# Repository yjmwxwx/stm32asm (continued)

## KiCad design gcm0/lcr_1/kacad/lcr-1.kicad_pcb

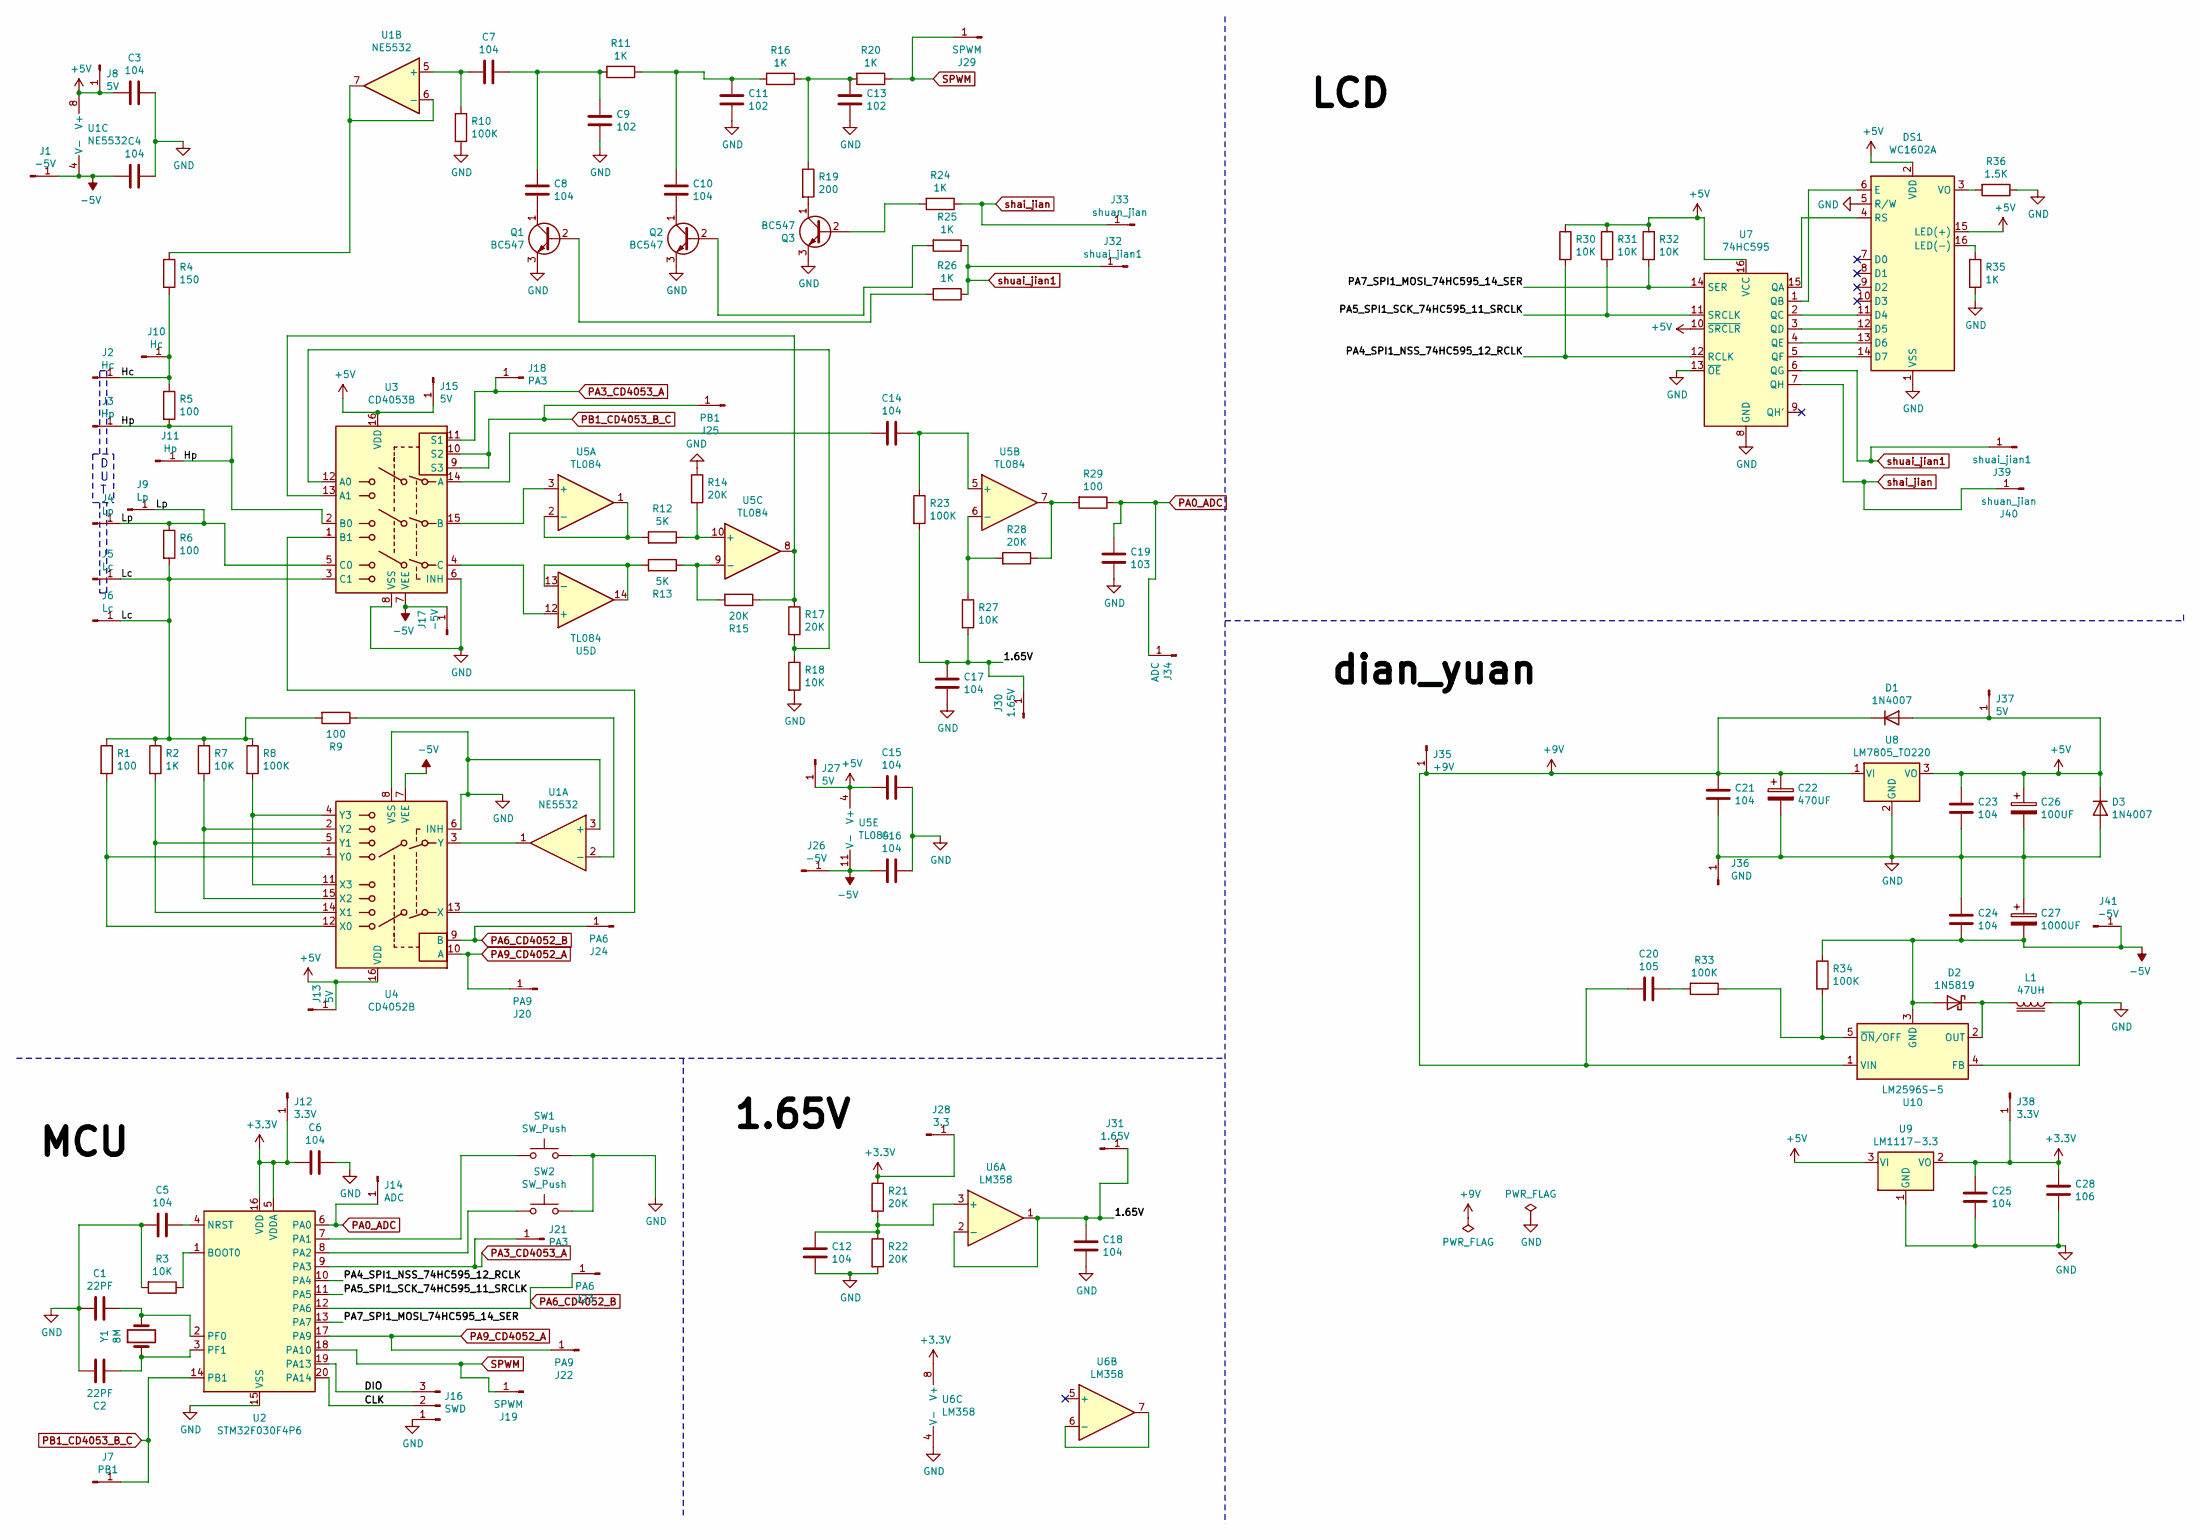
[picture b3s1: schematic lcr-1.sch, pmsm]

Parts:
C1, C2: 22PF; C_0805_2012Metric_Pad1.18x1.45mm_HandSolder
C3, C4, C5, C6, C7, C8, C10, C12, C14, C15, C16, C17, C18, C21, C23, C24, C25: 104; C_Disc_D3.0mm_W2.0mm_P2.50mm
C9, C11, C13: 102; C_Disc_D3.0mm_W2.0mm_P2.50mm
C19: 103; C_Disc_D3.0mm_W2.0mm_P2.50mm
C20: 105; C_0805_2012Metric_Pad1.18x1.45mm_HandSolder
C22: 470UF; CP_Radial_D10.0mm_P3.50mm
C26: 100UF; CP_Radial_D10.0mm_P3.50mm
C27: 1000UF; CP_Radial_D10.0mm_P3.50mm
C28: 106; C_0805_2012Metric_Pad1.18x1.45mm_HandSolder
D1, D3: 1N4007; D_DO-41_SOD81_P10.16mm_Horizontal
D2: 1N5819; D_SMA_Handsoldering
DS1: WC1602A
J1, J17, J26, J41: -5V; Pin_D0.7mm_L6.5mm_W1.8mm_FlatFork
J2, J10: Hc; Pin_D1.3mm_L11.0mm_LooseFit
J3, J11: Hp; Pin_D1.3mm_L11.0mm_LooseFit
J4, J9: Lp; Pin_D1.3mm_L11.0mm_LooseFit
J5, J6: Lc; Pin_D1.3mm_L11.0mm_LooseFit
J7, J25: PB1; Pin_D0.7mm_L6.5mm_W1.8mm_FlatFork
J8, J13, J15, J27, J37: 5V; Pin_D0.7mm_L6.5mm_W1.8mm_FlatFork
J12, J38: 3.3V; Pin_D0.7mm_L6.5mm_W1.8mm_FlatFork
J14, J34: ADC; Pin_D0.7mm_L6.5mm_W1.8mm_FlatFork
J16: SWD; PinHeader_1x03_P2.54mm_Vertical
J18, J21: PA3; Pin_D0.7mm_L6.5mm_W1.8mm_FlatFork
J19, J29: SPWM; Pin_D0.7mm_L6.5mm_W1.8mm_FlatFork
J20, J22: PA9; Pin_D0.7mm_L6.5mm_W1.8mm_FlatFork
J23, J24: PA6; Pin_D0.7mm_L6.5mm_W1.8mm_FlatFork
J28: 3.3; Pin_D0.7mm_L6.5mm_W1.8mm_FlatFork
J30, J31: 1.65V; Pin_D0.7mm_L6.5mm_W1.8mm_FlatFork
J32, J39: shuai_jian1; Pin_D0.7mm_L6.5mm_W1.8mm_FlatFork
J33, J40: shuan_jian; Pin_D0.7mm_L6.5mm_W1.8mm_FlatFork
J35: +9V; Pin_D1.3mm_L11.0mm_LooseFit
J36: GND; Pin_D1.3mm_L11.0mm_LooseFit
L1: 47UH; L_Radial_D10.0mm_P5.00mm_Fastron_07P
Q1, Q2, Q3: BC547; TO-92_Inline_Wide
R1, R5, R6, R9, R29: 100; R_Axial_DIN0204_L3.6mm_D1.6mm_P2.54mm_Vertical
R2, R11, R16, R20, R24, R25, R26, R35: 1K; R_Axial_DIN0204_L3.6mm_D1.6mm_P2.54mm_Vertical
R3, R7, R18, R27, R30, R31, R32: 10K; R_Axial_DIN0204_L3.6mm_D1.6mm_P2.54mm_Vertical
R4: 150; R_Axial_DIN0204_L3.6mm_D1.6mm_P2.54mm_Vertical
R8, R10, R23, R33, R34: 100K; R_Axial_DIN0204_L3.6mm_D1.6mm_P2.54mm_Vertical
R12, R13: 5K; R_Axial_DIN0204_L3.6mm_D1.6mm_P2.54mm_Vertical
R14, R15, R17, R21, R22, R28: 20K; R_Axial_DIN0204_L3.6mm_D1.6mm_P2.54mm_Vertical
R19: 200; R_Axial_DIN0204_L3.6mm_D1.6mm_P2.54mm_Vertical
R36: 1.5K; R_Axial_DIN0204_L3.6mm_D1.6mm_P2.54mm_Vertical
SW1, SW2: SW_Push; SW_PUSH_6mm_H7.3mm
U1: NE5532; DIP-8_W7.62mm
U2: STM32F030F4P6; TSSOP-20_4.4x6.5mm_P0.65mm
U3: CD4053B; DIP-16_W7.62mm
U4: CD4052B; DIP-16_W7.62mm
U5: TL084; DIP-14_W7.62mm
U6: LM358; DIP-8_W7.62mm
U7: 74HC595; DIP-16_W7.62mm
U8: LM7805_TO220; TO-220-3_Vertical
U9: LM1117-3.3; SOT-223-3_TabPin2
U10: LM2596S-5; TO-263-5_TabPin3
Y1: 8M; Crystal_HC49-4H_Vertical

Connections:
+3V3: C6.2, C25.1, C28.1, J12.1, J28.1, J38.1, R21.1, U2.5 (VDDA), U2.16 (VDD), U6.8 (V+), U9.2 (VO)
+5V: C3.2, C15.2, C23.1, C26.1, D1.2 (A), D3.1 (K), DS1.2 (VDD), DS1.15 (LED(+)), J8.1, J13.1, J15.1, J27.1, J37.1, R30.1, R31.1, R32.1, U1.8 (V+), U3.16 (VDD), U4.16 (VDD), U5.4 (V+), U7.10 (~SRCLR), U7.16 (VCC), U8.3 (VO), U9.3 (VI)
+9V: C20.2, C21.1, C22.1, D1.1 (K), J35.1, U8.1 (VI), U10.1 (VIN)
-5V: C4.2, C16.2, C24.2, C27.2, D2.2 (A), J1.1, J17.1, J26.1, J41.1, R34.1, U1.4 (V-), U3.7 (VEE), U4.7 (VEE), U5.11 (V-), U10.3 (GND)
/1.65V: C17.1, C18.1, J30.1, J31.1, R23.2, R27.2, U6.1, U6.2 (-)
/CLK: J16.2, U2.20 (PA14)
/DIO: J16.3, U2.19 (PA13)
/Hc: J2.1, J10.1, R4.2, R5.1
/Hp: J3.1, J11.1, R5.2, U3.2 (B0)
/Lc: J5.1, J6.1, R1.1, R2.1, R6.2, R7.1, R8.1, R9.2, U3.3 (C1)
/Lp: J4.1, J9.1, R6.1, U3.5 (C0)
/PA4_SPI1_NSS_74HC595_12_RCLK: R30.2, U2.10 (PA4), U7.12 (RCLK)
/PA5_SPI1_SCK_74HC595_11_SRCLK: R31.2, U2.11 (PA5), U7.11 (SRCLK)
/PA7_SPI1_MOSI_74HC595_14_SER: R32.2, U2.13 (PA7), U7.14 (SER)
GND: C1.2, C2.1, C3.1, C4.1, C5.2, C6.1, C9.2, C11.2, C12.2, C13.2, C15.1, C16.1, C17.2, C18.2, C19.2, C21.2, C22.2, C23.2, C24.1, C25.2, C26.2, C27.1, C28.2, D3.2 (A), DS1.1 (VSS), DS1.5 (R/W), J16.1, J36.1, L1.1, Q1.3 (E), Q2.3 (E), Q3.3 (E), R3.2, R10.2, R14.1, R18.2, R22.2, R35.2, R36.1, SW1.2, SW2.2, U1.3 (+), U2.15 (VSS), U3.6 (INH), U3.8 (VSS), U4.6 (INH), U4.8 (VSS), U6.4 (V-), U7.8 (GND), U7.13 (~OE), U8.2 (GND), U9.1 (GND), U10.4 (FB)
unnamed: C1.1, U2.2 (PF0), Y1.2
unnamed: C2.2, U2.3 (PF1), Y1.1
unnamed: C5.1, U2.4 (NRST)
unnamed: C7.1, C8.1, C9.1, R11.2
unnamed: C7.2, R10.1, U1.5 (+)
unnamed: C8.2, Q1.1 (C)
unnamed: C10.1, C11.1, R11.1, R16.2
unnamed: C10.2, Q2.1 (C)
unnamed: C12.1, R21.2, R22.1, U6.3 (+)
unnamed: C13.1, R16.1, R19.1, R20.2
unnamed: C14.1, R23.1, U5.5 (+)
unnamed: C14.2, U3.14 (A)
unnamed: C20.1, R33.2
unnamed: D2.1 (K), L1.2, U10.2 (OUT)
unnamed: DS1.3 (VO), R36.2
unnamed: DS1.4 (RS), U7.15 (QA)
unnamed: DS1.6 (E), U7.1 (QB)
unnamed: DS1.11 (D4), U7.2 (QC)
unnamed: DS1.12 (D5), U7.3 (QD)
unnamed: DS1.13 (D6), U7.4 (QE)
unnamed: DS1.14 (D7), U7.5 (QF)
unnamed: DS1.16 (LED(-)), R35.1
unnamed: Q1.2 (B), R26.2
unnamed: Q2.2 (B), R25.2
unnamed: Q3.1 (C), R19.2
unnamed: Q3.2 (B), R24.2
unnamed: R1.2, U4.1 (Y0), U4.12 (X0)
unnamed: R2.2, U4.5 (Y1), U4.14 (X1)
unnamed: R3.1, U2.1 (BOOT0)
unnamed: R4.1, U1.6 (-), U1.7
unnamed: R7.2, U4.2 (Y2), U4.15 (X2)
unnamed: R8.2, U4.4 (Y3), U4.11 (X3)
unnamed: R9.1, U1.2 (-)
unnamed: R12.1, R14.2, U5.10 (+)
unnamed: R12.2, U5.1, U5.2 (-)
unnamed: R13.1, R15.2, U5.9 (-)
unnamed: R13.2, U5.13 (-), U5.14
unnamed: R15.1, R17.1, U3.13 (A1), U5.8
unnamed: R17.2, R18.1, U3.12 (A0)
unnamed: R27.1, R28.2, U5.6 (-)
unnamed: R28.1, R29.2, U5.7
unnamed: R33.1, R34.2, U10.5 (~ON~/OFF)
unnamed: SW1.1, U2.7 (PA1)
unnamed: SW2.1, U2.8 (PA2)
unnamed: U1.1, U4.3 (Y)
unnamed: U3.1 (B1), U4.13 (X)
unnamed: U3.4 (C), U5.12 (+)
unnamed: U3.15 (B), U5.3 (+)
unnamed: U6.6 (-), U6.7
PA0_ADC: C19.1, J14.1, J34.1, R29.1, U2.6 (PA0)
PA3_CD4053_A: J18.1, J21.1, U2.9 (PA3), U3.11 (S1)
PA6_CD4052_B: J23.1, J24.1, U2.12 (PA6), U4.9 (B)
PA9_CD4052_A: J20.1, J22.1, U2.17 (PA9), U4.10 (A)
PB1_CD4053_B_C: J7.1, J25.1, U2.14 (PB1), U3.9 (S3), U3.10 (S2)
SPWM: J19.1, J29.1, R20.1, U2.18 (PA10)
shai_jian: J33.1, J40.1, R24.1, U7.7 (QH)
shuai_jian1: J32.1, J39.1, R25.1, R26.1, U7.6 (QG)

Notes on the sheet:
D U T

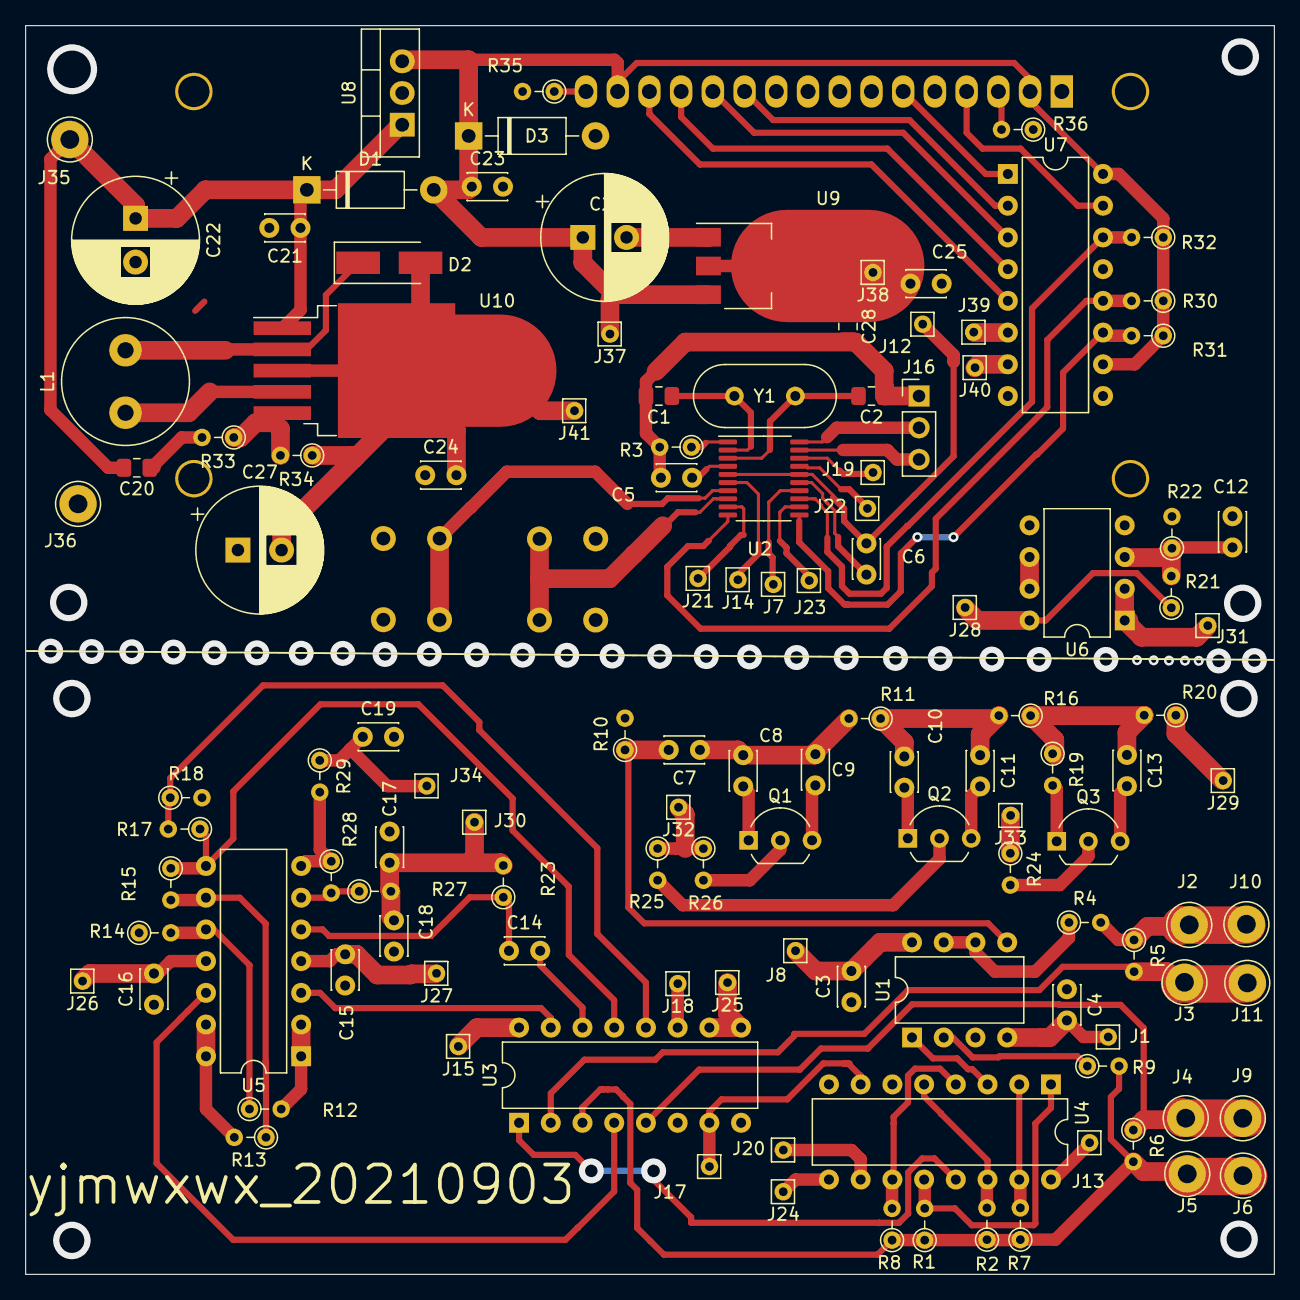
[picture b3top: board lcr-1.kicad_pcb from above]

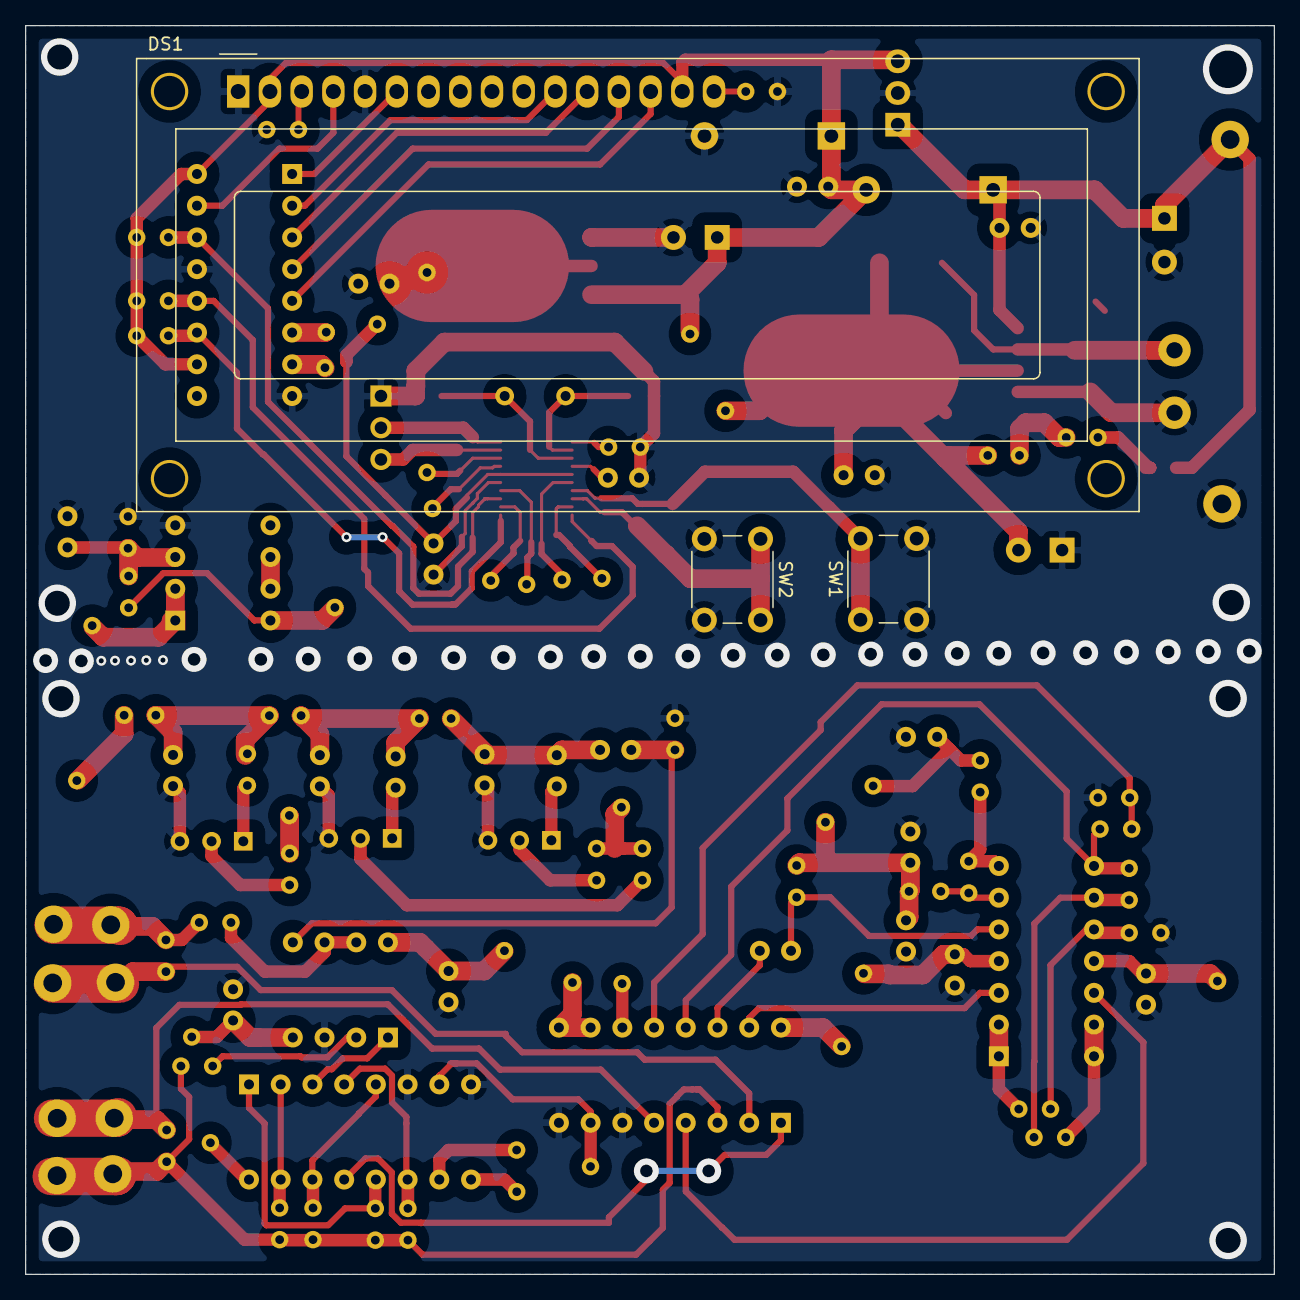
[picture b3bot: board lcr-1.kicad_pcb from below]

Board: 2 copper layers, 100.0 x 100.0 mm, 126 parts (3 on the bottom side), 72 nets.

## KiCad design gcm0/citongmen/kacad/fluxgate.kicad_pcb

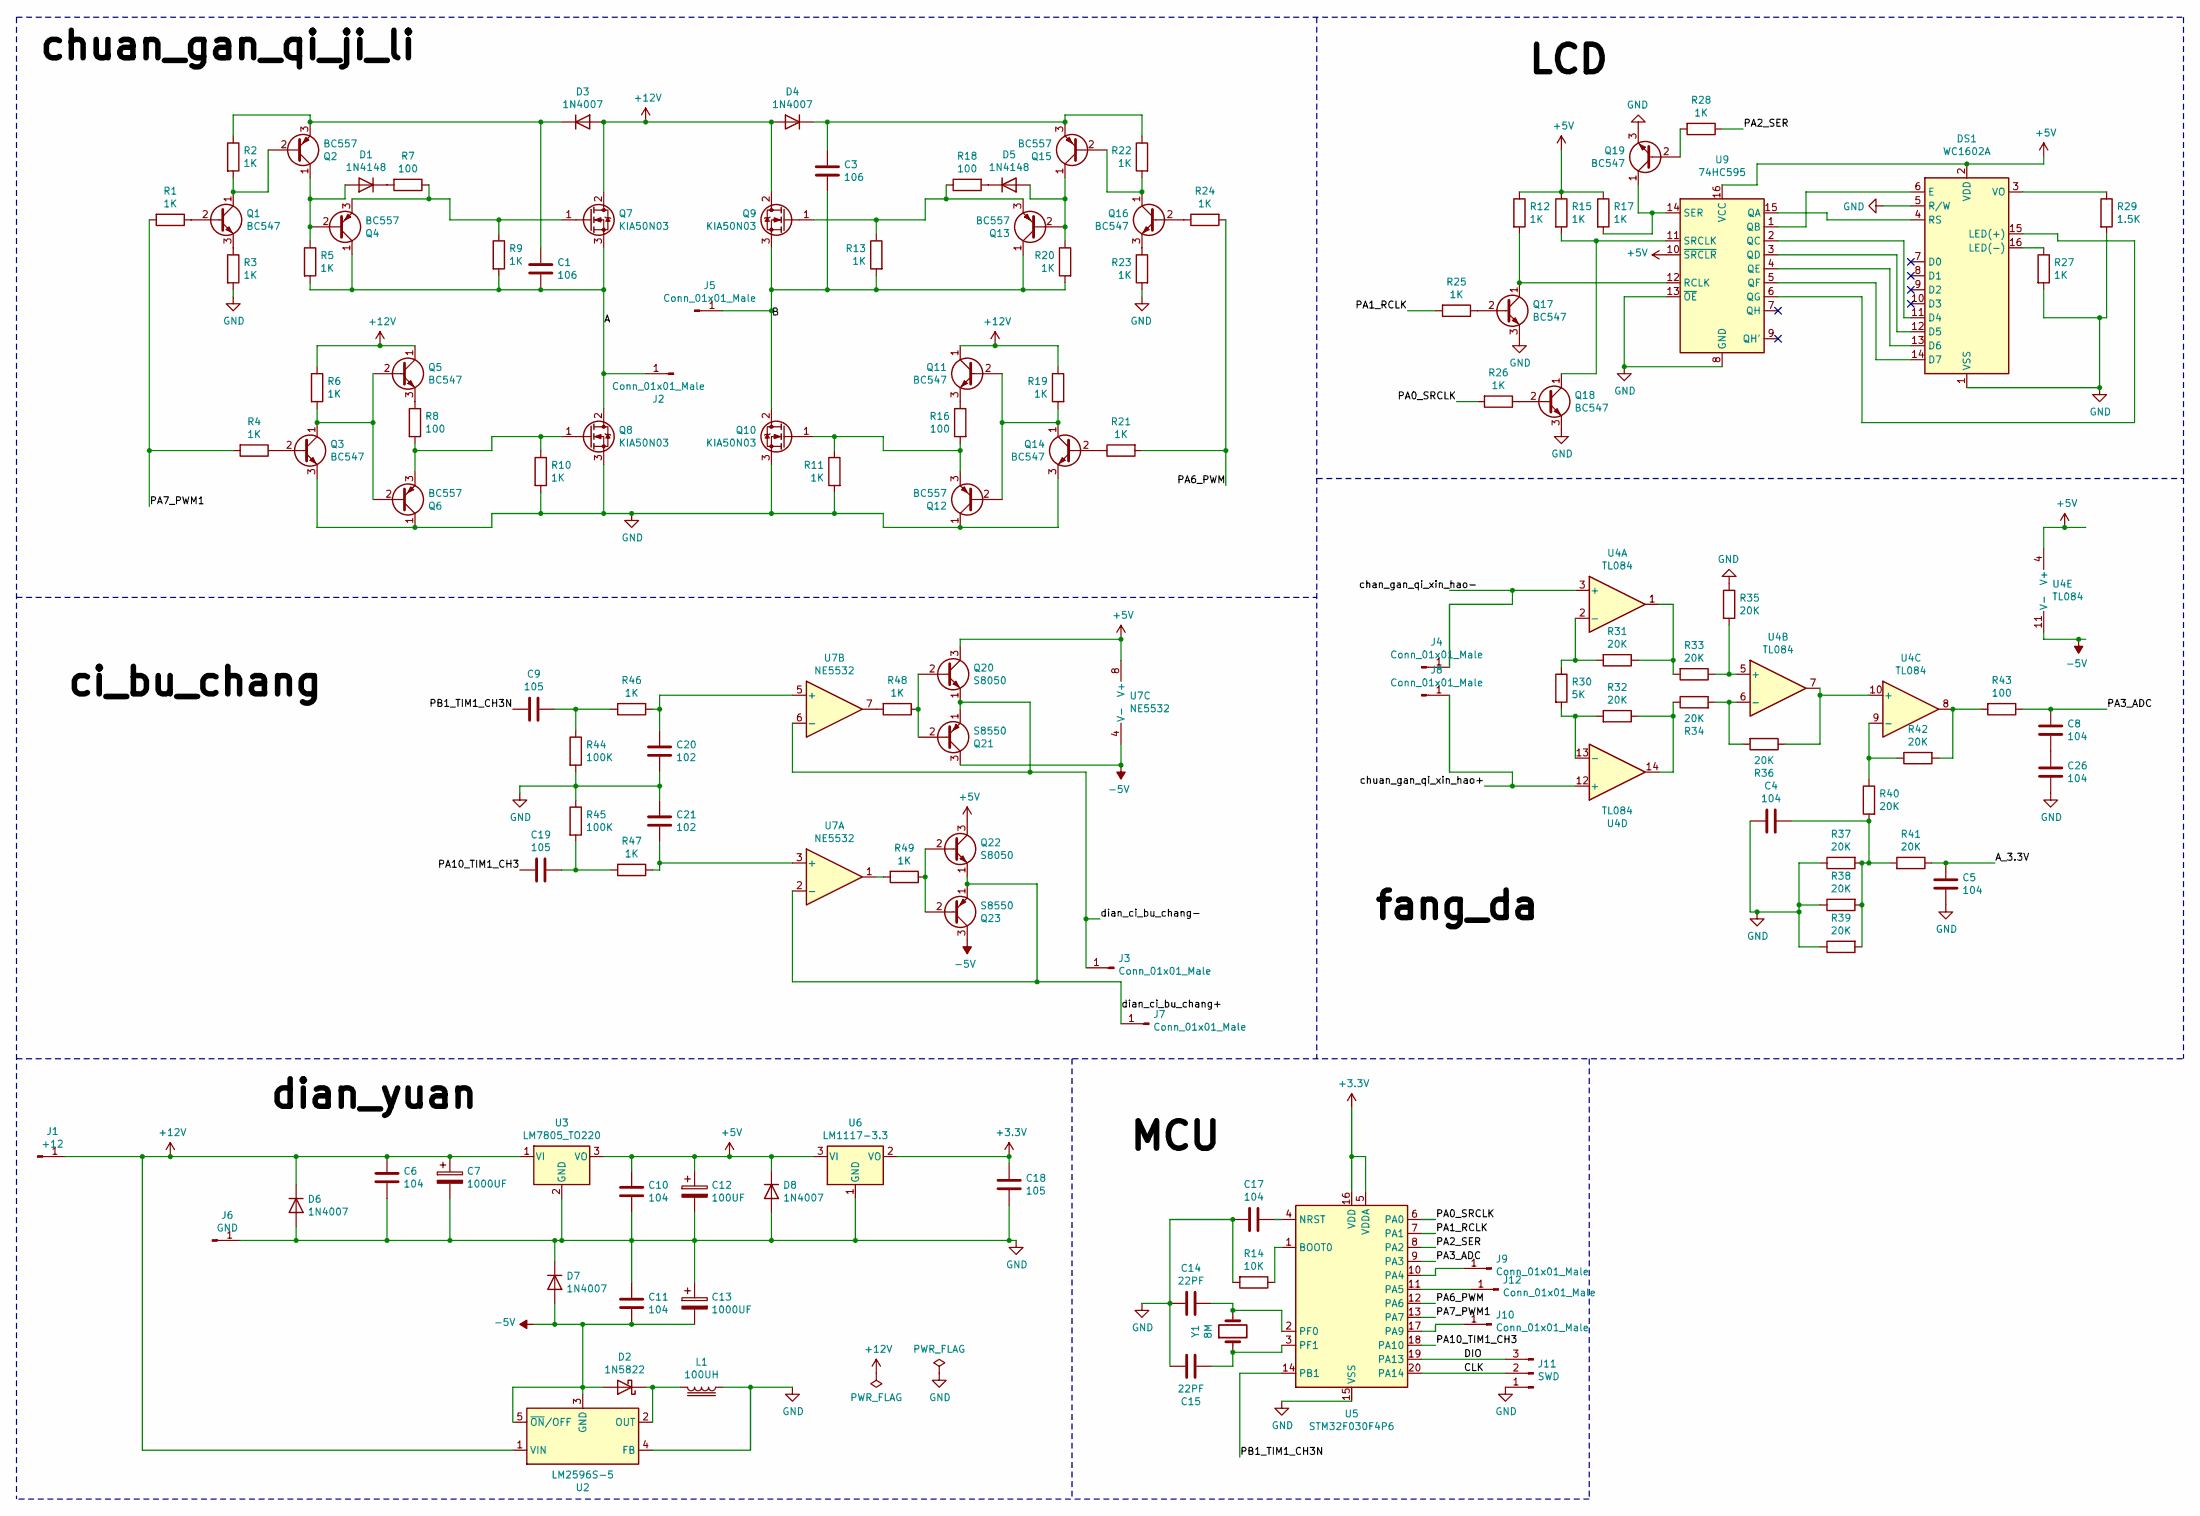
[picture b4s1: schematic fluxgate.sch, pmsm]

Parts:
C1, C3: 106; C_0805_2012Metric_Pad1.18x1.45mm_HandSolder
C4, C5, C6, C8, C10, C11, C17, C26: 104; C_Disc_D3.0mm_W2.0mm_P2.50mm
C7, C13: 1000UF; CP_Radial_D10.0mm_P3.50mm
C9, C18, C19: 105; C_0805_2012Metric_Pad1.18x1.45mm_HandSolder
C12: 100UF; CP_Radial_D10.0mm_P3.50mm
C14, C15: 22PF; C_0805_2012Metric_Pad1.18x1.45mm_HandSolder
C20, C21: 102; C_Disc_D3.0mm_W2.0mm_P2.50mm
D1, D5: 1N4148; D_DO-35_SOD27_P7.62mm_Horizontal
D2: 1N5822; D_DO-201AD_P15.24mm_Horizontal
D3, D4, D6, D7, D8: 1N4007; D_DO-41_SOD81_P10.16mm_Horizontal
DS1: WC1602A; PinHeader_1x16_P2.54mm_Vertical
J1: +12; PinHeader_1x01_P2.54mm_Vertical
J2, J3, J4, J5, J7, J8: Conn_01x01_Male; PinHeader_1x01_P2.54mm_Vertical
J6: GND; PinHeader_1x01_P2.54mm_Vertical
J9, J10, J12: Conn_01x01_Male; SolderWirePad_1x01_SMD_1x2mm
J11: SWD; PinHeader_1x03_P2.54mm_Vertical
L1: 100UH; L_Radial_D10.0mm_P5.00mm_Fastron_07P
Q1, Q3, Q5, Q11, Q14, Q16, Q17, Q18, Q19: BC547; TO-92_Inline_Wide
Q2, Q4, Q6, Q12, Q13, Q15: BC557; TO-92_Inline_Wide
Q7, Q8, Q9, Q10: KIA50N03; TO-252-2
Q20, Q22: S8050; TO-92_Inline_Wide
Q21, Q23: S8550; TO-92_Inline_Wide
R1, R2, R3, R4, R5, R6, R9, R10, R11, R12, R13, R15, R17, R19, R20, R21, R22, R23, R24, R25, R26, R27, R28, R46, R47, R48, R49: 1K; R_Axial_DIN0207_L6.3mm_D2.5mm_P5.08mm_Vertical
R7, R8, R16, R18, R43: 100; R_Axial_DIN0207_L6.3mm_D2.5mm_P5.08mm_Vertical
R14: 10K; R_Axial_DIN0207_L6.3mm_D2.5mm_P5.08mm_Vertical
R29: 1.5K; R_Axial_DIN0207_L6.3mm_D2.5mm_P5.08mm_Vertical
R30: 5K; R_Axial_DIN0207_L6.3mm_D2.5mm_P5.08mm_Vertical
R31, R32, R33, R34, R35, R36, R37, R38, R39, R40, R41, R42: 20K; R_Axial_DIN0207_L6.3mm_D2.5mm_P5.08mm_Vertical
R44, R45: 100K; R_Axial_DIN0207_L6.3mm_D2.5mm_P5.08mm_Vertical
U2: LM2596S-5; TO-263-5_TabPin3
U3: LM7805_TO220; TO-220-3_Vertical
U4: TL084; DIP-14_W7.62mm
U5: STM32F030F4P6; TSSOP-20_4.4x6.5mm_P0.65mm
U6: LM1117-3.3; SOT-223-3_TabPin2
U7: NE5532; DIP-8_W7.62mm
U9: 74HC595; DIP-16_W7.62mm
Y1: 8M; Crystal_HC49-4H_Vertical

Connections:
+3V3: C18.1, U5.5 (VDDA), U5.16 (VDD), U6.2 (VO)
+5V: C10.1, C12.1, D8.1 (K), DS1.2 (VDD), Q20.3 (C), Q22.3 (C), R12.1, R15.1, R17.1, U3.3 (VO), U4.4 (V+), U6.3 (VI), U7.8 (V+), U9.10 (~SRCLR), U9.16 (VCC)
+12V: C6.1, C7.1, D3.2 (A), D4.2 (A), D6.1 (K), J1.1, Q5.1 (C), Q7.2 (D), Q9.2 (D), Q11.1 (C), R6.1, R19.1, U2.1 (VIN), U3.1 (VI)
-5V: C11.2, C13.2, D2.2 (A), D7.2 (A), Q21.3 (C), Q23.3 (C), U2.3 (GND), U2.5 (~ON~/OFF), U4.11 (V-), U7.4 (V-)
/A: C1.2, J2.1, Q4.1 (C), Q7.3 (S), Q8.2 (D), R5.2, R9.2
/A_3.3V: C5.2, R41.1
/B: C3.2, J5.1, Q9.3 (S), Q10.2 (D), Q13.1 (C), R13.2, R20.2
/CLK: J11.2, U5.20 (PA14)
/DIO: J11.3, U5.19 (PA13)
/PA0_SRCLK: R26.2, U5.6 (PA0)
/PA1_RCLK: R25.2, U5.7 (PA1)
/PA2_SER: R28.1, U5.8 (PA2)
/PA3_ADC: C8.1, R43.1, U5.9 (PA3)
/PA6_PWM: R21.2, R24.2, U5.12 (PA6)
/PA7_PWM1: R1.2, R4.2, U5.13 (PA7)
/PA10_TIM1_CH3: C19.2, U5.18 (PA10)
/PB1_TIM1_CH3N: C9.2, U5.14 (PB1)
/chan_gan_qi_xin_hao-: J4.1, U4.3 (+)
/chuan_gan_qi_xin_hao+: J8.1, U4.12 (+)
/dian_ci_bu_chang+: J7.1, Q22.1 (E), Q23.1 (E), U7.2 (-)
/dian_ci_bu_chang-: J3.1, Q20.1 (E), Q21.1 (E), U7.6 (-)
GND: C4.2, C5.1, C6.2, C7.2, C10.2, C11.1, C12.2, C13.1, C14.2, C15.1, C17.2, C18.2, C20.2, C21.1, C26.2, D6.2 (A), D7.1 (K), D8.2 (A), DS1.1 (VSS), DS1.5 (R/W), J6.1, J11.1, L1.1, Q3.3 (E), Q6.1 (C), Q8.3 (S), Q10.3 (S), Q12.1 (C), Q14.3 (E), Q17.3 (E), Q18.3 (E), Q19.3 (E), R3.2, R10.2, R11.2, R14.2, R23.2, R27.2, R29.2, R35.1, R37.1, R38.1, R39.1, R44.2, R45.1, U2.4 (FB), U3.2 (GND), U5.15 (VSS), U6.1 (GND), U9.8 (GND), U9.13 (~OE)
unnamed: C1.1, D3.1 (K), Q2.3 (E), R2.1
unnamed: C3.1, D4.1 (K), Q15.3 (E), R22.1
unnamed: C4.1, R37.2, R38.2, R39.2, R40.2, R41.2
unnamed: C9.1, R44.1, R46.2
unnamed: C14.1, U5.2 (PF0), Y1.2
unnamed: C15.2, U5.3 (PF1), Y1.1
unnamed: C17.1, U5.4 (NRST)
unnamed: C19.1, R45.2, R47.2
unnamed: C20.1, R46.1, U7.5 (+)
unnamed: C21.2, R47.1, U7.3 (+)
unnamed: C8.2, C26.1
unnamed: D1.1 (K), R7.2
unnamed: D1.2 (A), Q2.1 (C), Q4.2 (B), R5.1
unnamed: D2.1 (K), L1.2, U2.2 (OUT)
unnamed: D5.1 (K), R18.2
unnamed: D5.2 (A), Q13.2 (B), Q15.1 (C), R20.1
unnamed: DS1.3 (VO), R29.1
unnamed: DS1.4 (RS), U9.15 (QA)
unnamed: DS1.6 (E), U9.1 (QB)
unnamed: DS1.11 (D4), U9.2 (QC)
unnamed: DS1.12 (D5), U9.3 (QD)
unnamed: DS1.13 (D6), U9.4 (QE)
unnamed: DS1.14 (D7), U9.5 (QF)
unnamed: DS1.15 (LED(+)), U9.6 (QG)
unnamed: DS1.16 (LED(-)), R27.1
unnamed: J9.1, U5.10 (PA4)
unnamed: J10.1, U5.17 (PA9)
unnamed: J12.1, U5.11 (PA5)
unnamed: Q1.1 (C), Q2.2 (B), R2.2
unnamed: Q1.2 (B), R1.1
unnamed: Q1.3 (E), R3.1
unnamed: Q3.1 (C), Q5.2 (B), Q6.2 (B), R6.2
unnamed: Q3.2 (B), R4.1
unnamed: Q4.3 (E), Q7.1 (G), R7.1, R9.1
unnamed: Q5.3 (E), R8.1
unnamed: Q6.3 (E), Q8.1 (G), R8.2, R10.1
unnamed: Q10.1 (G), Q12.3 (E), R11.1, R16.2
unnamed: Q11.2 (B), Q12.2 (B), Q14.1 (C), R19.2
unnamed: Q11.3 (E), R16.1
unnamed: Q9.1 (G), Q13.3 (E), R13.1, R18.1
unnamed: Q14.2 (B), R21.1
unnamed: Q15.2 (B), Q16.1 (C), R22.2
unnamed: Q16.2 (B), R24.1
unnamed: Q16.3 (E), R23.1
unnamed: Q17.1 (C), R12.2, U9.12 (RCLK)
unnamed: Q17.2 (B), R25.1
unnamed: Q18.1 (C), R15.2, U9.11 (SRCLK)
unnamed: Q18.2 (B), R26.1
unnamed: Q19.1 (C), R17.2, U9.14 (SER)
unnamed: Q19.2 (B), R28.2
unnamed: Q20.2 (B), Q21.2 (B), R48.1
unnamed: Q22.2 (B), Q23.2 (B), R49.1
unnamed: R14.1, U5.1 (BOOT0)
unnamed: R30.1, R31.2, U4.2 (-)
unnamed: R30.2, R32.2, U4.13 (-)
unnamed: R31.1, R33.2, U4.1
unnamed: R32.1, R34.1, U4.14
unnamed: R33.1, R35.2, U4.5 (+)
unnamed: R34.2, R36.2, U4.6 (-)
unnamed: R36.1, U4.7, U4.10 (+)
unnamed: R40.1, R42.1, U4.9 (-)
unnamed: R42.2, R43.2, U4.8
unnamed: R48.2, U7.7
unnamed: R49.2, U7.1

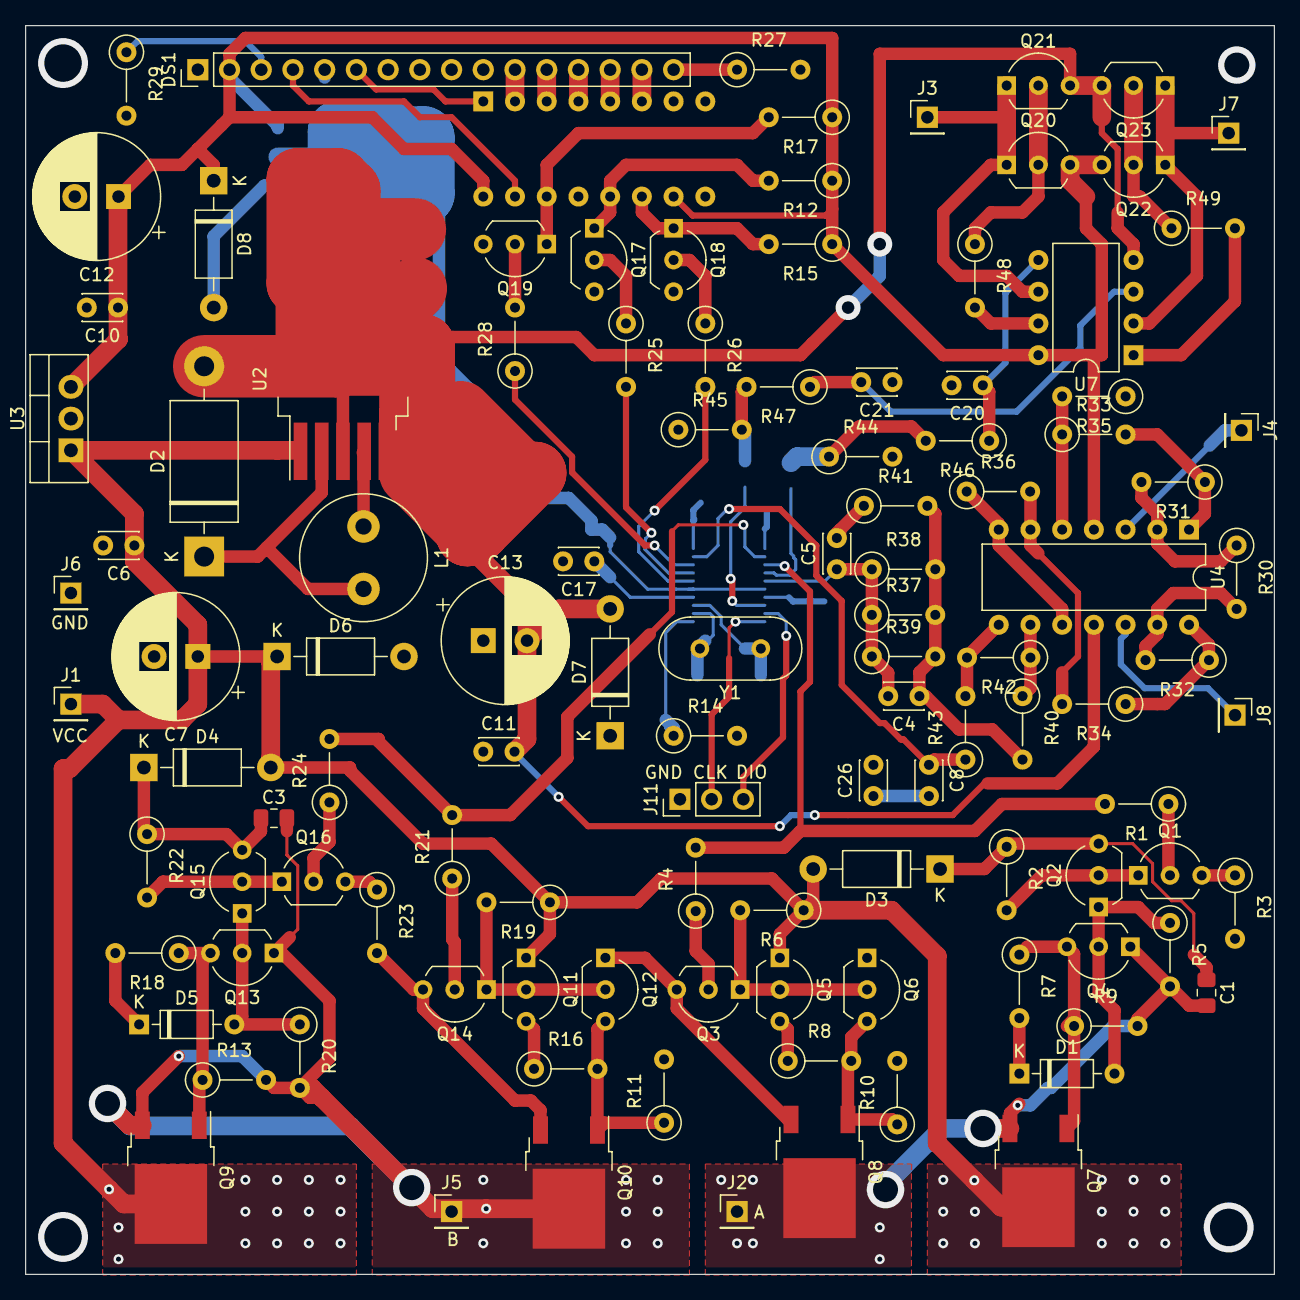
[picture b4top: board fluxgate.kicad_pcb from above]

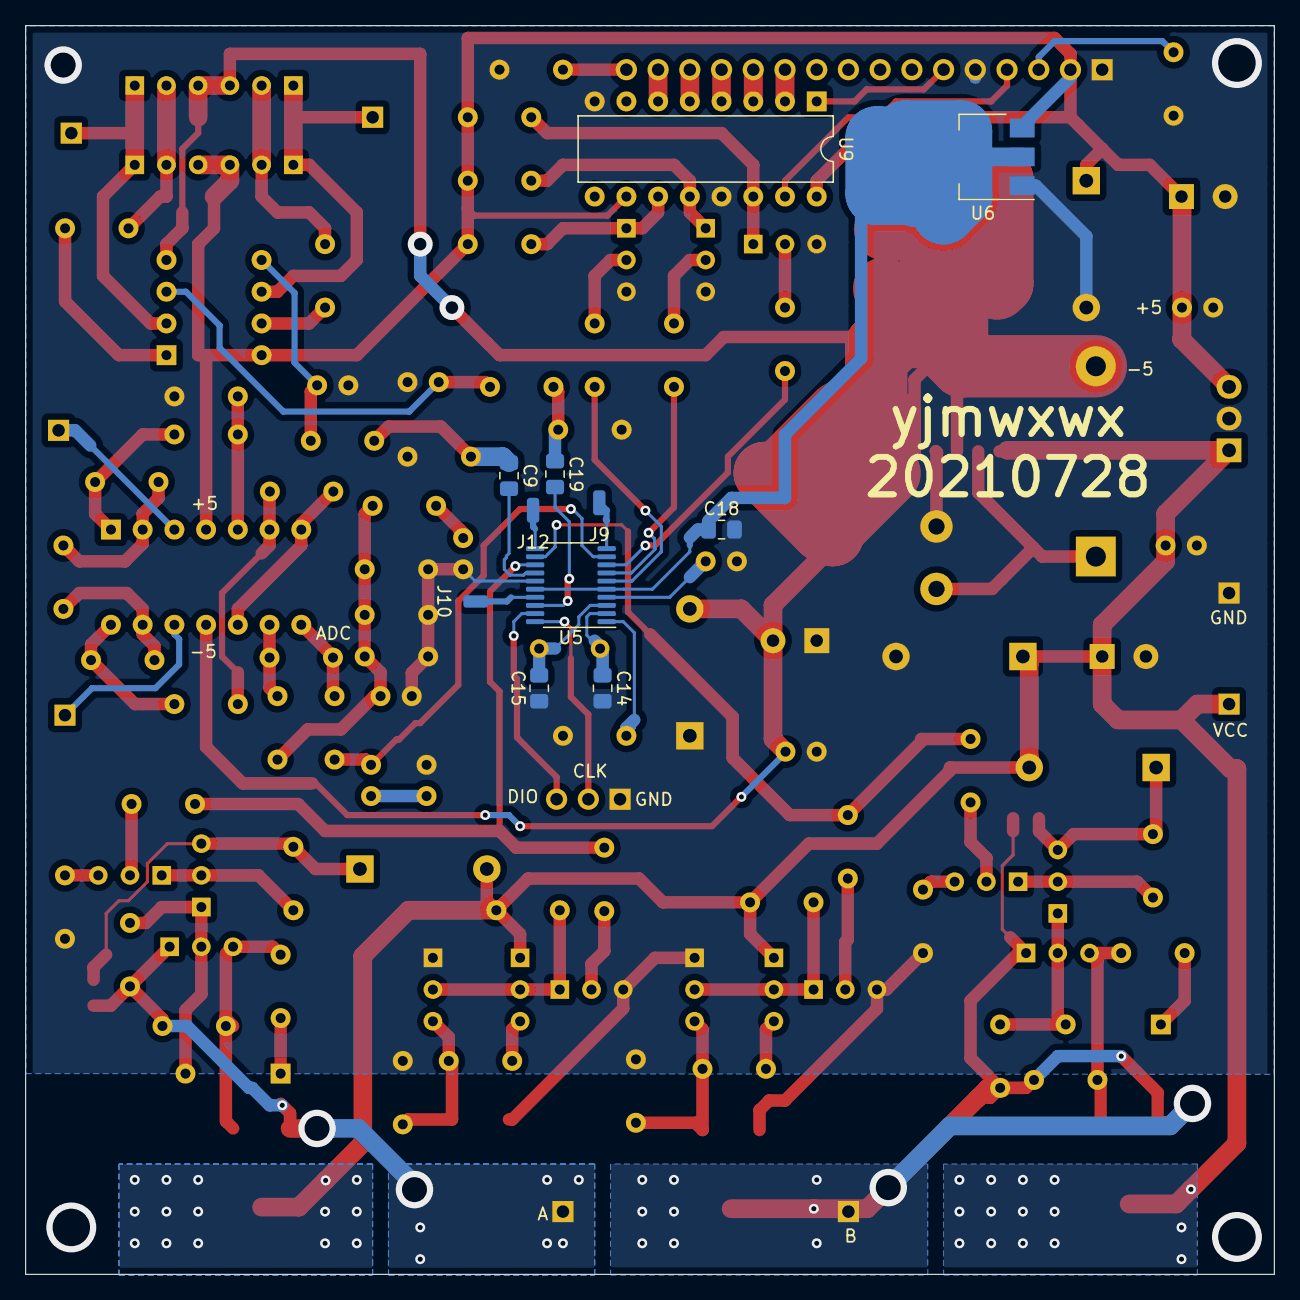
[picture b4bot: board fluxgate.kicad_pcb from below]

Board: 2 copper layers, 100.0 x 100.0 mm, 122 parts (11 on the bottom side), 86 nets.
